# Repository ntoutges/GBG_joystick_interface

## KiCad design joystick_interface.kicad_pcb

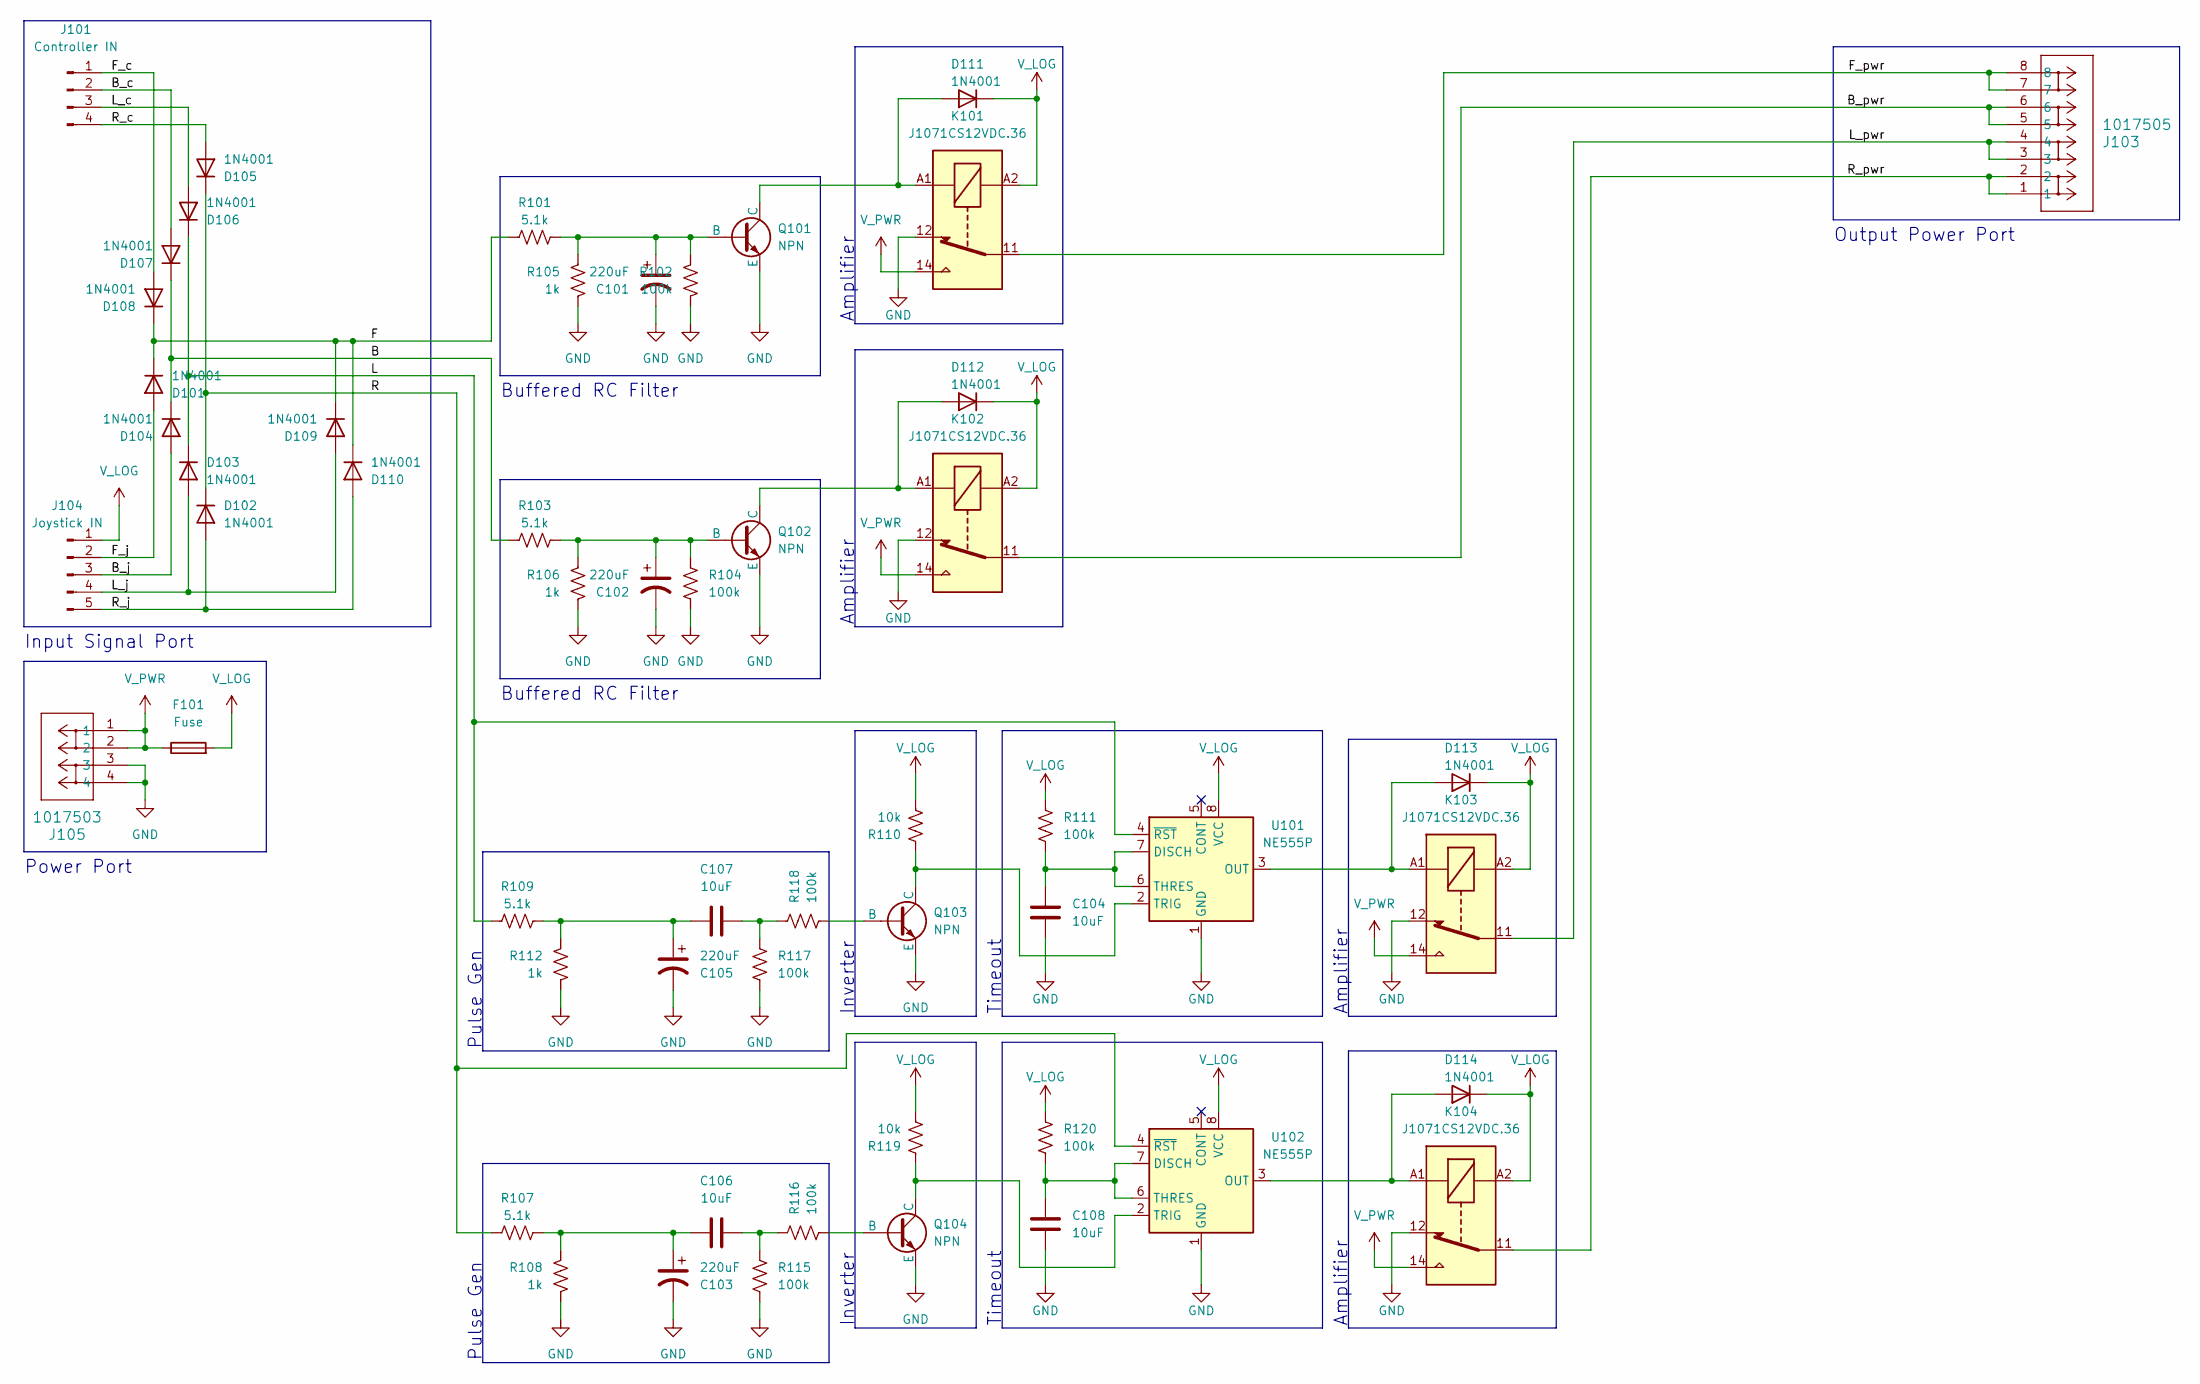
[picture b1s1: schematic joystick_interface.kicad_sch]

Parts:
C101, C102, C103, C105: 220uF; C_Radial_D5.0mm_H11.0mm_P2.00mm
C104, C106, C107, C108: 10uF; C_Disc_D3.4mm_W2.1mm_P2.50mm
D101, D102, D103, D104, D105, D106, D107, D108, D109, D110, D111, D112, D113, D114: 1N4001; D_DO-41_SOD81_P10.16mm_Horizontal
F101: Fuse; Fuseholder_Clip-5x20mm_Eaton_1A5601-01_Inline_P20.80x6.76mm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
J101: Controller IN; JST_EH_B4B-EH-A_1x04_P2.50mm_Vertical
J103: 1017505; CONN_1017493
J104: Joystick IN; JST_EH_B5B-EH-A_1x05_P2.50mm_Vertical
J105: 1017503; CONN_1017491
K101, K102, K103, K104: J1071CS12VDC.36; Relay_SPDT_Hongfa_HF3F-L-xx-1ZL1T
Q101, Q102, Q103, Q104: NPN; TO-92_Wide
R101, R103: 5.1k; R_Axial_DIN0207_L6.3mm_D2.5mm_P10.16mm_Horizontal
R102, R104: 100k; R_Axial_DIN0207_L6.3mm_D2.5mm_P10.16mm_Horizontal
R105, R106: 1k; R_Axial_DIN0207_L6.3mm_D2.5mm_P10.16mm_Horizontal
R107, R109: 5.1k; R_Axial_DIN0204_L3.6mm_D1.6mm_P1.90mm_Vertical
R108, R112: 1k; R_Axial_DIN0204_L3.6mm_D1.6mm_P1.90mm_Vertical
R110, R119: 10k; R_Axial_DIN0204_L3.6mm_D1.6mm_P1.90mm_Vertical
R111, R115, R116, R117, R118, R120: 100k; R_Axial_DIN0204_L3.6mm_D1.6mm_P1.90mm_Vertical
U101, U102: NE555P; DIP-8_W7.62mm

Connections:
/B: D104.1 (K), D107.1 (K), R103.1
/B_c: D107.2 (A), J101.2
/B_j: D104.2 (A), J104.3
/B_pwr: J103.5, J103.6, K102.11
/F: D101.1 (K), D108.1 (K), D109.1 (K), D110.1 (K), R101.1
/F_c: D108.2 (A), J101.1
/F_j: D101.2 (A), J104.2
/F_pwr: J103.7, J103.8, K101.11
/L: D103.1 (K), D106.1 (K), R109.1, U101.4 (~RST)
/L_c: D106.2 (A), J101.3
/L_j: D103.2 (A), D109.2 (A), J104.4
/L_pwr: J103.3, J103.4, K103.11
/R: D102.1 (K), D105.1 (K), R107.1, U102.4 (~RST)
/R_c: D105.2 (A), J101.4
/R_j: D102.2 (A), D110.2 (A), J104.5
/R_pwr: J103.1, J103.2, K104.11
GND: C101.2, C102.2, C103.2, C104.1, C105.2, C108.1, J105.3, J105.4, K101.12, K102.12, K103.12, K104.12, Q101.3 (E), Q102.3 (E), Q103.3 (E), Q104.3 (E), R102.1, R104.1, R105.2, R106.2, R108.2, R112.2, R115.1, R117.1, U101.1 (GND), U102.1 (GND)
unnamed: C103.1, C106.1, R107.2, R108.1
unnamed: C105.1, C107.1, R109.2, R112.1
unnamed: C106.2, R115.2, R116.2
unnamed: C107.2, R117.2, R118.2
unnamed: D111.2 (A), K101.A1, Q101.1 (C)
unnamed: D112.2 (A), K102.A1, Q102.1 (C)
unnamed: D113.2 (A), K103.A1, U101.3 (OUT)
unnamed: D114.2 (A), K104.A1, U102.3 (OUT)
unnamed: C101.1, Q101.2 (B), R101.2, R102.2, R105.1
unnamed: C102.1, Q102.2 (B), R103.2, R104.2, R106.1
unnamed: Q103.2 (B), R118.1
unnamed: Q103.1 (C), R110.1, U101.2 (TRIG)
unnamed: Q104.2 (B), R116.1
unnamed: Q104.1 (C), R119.1, U102.2 (TRIG)
unnamed: C104.2, R111.2, U101.6 (THRES), U101.7 (DISCH)
unnamed: C108.2, R120.2, U102.6 (THRES), U102.7 (DISCH)
V_LOG: D111.1 (K), D112.1 (K), D113.1 (K), D114.1 (K), F101.2, J104.1, K101.A2, K102.A2, K103.A2, K104.A2, R110.2, R111.1, R119.2, R120.1, U101.8 (VCC), U102.8 (VCC)
V_PWR: F101.1, J105.1, J105.2, K101.14, K102.14, K103.14, K104.14

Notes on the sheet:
Amplifier
Buffered RC Filter
Power Port
Inverter
Input Signal Port
Pulse Gen
Output Power Port
Timeout

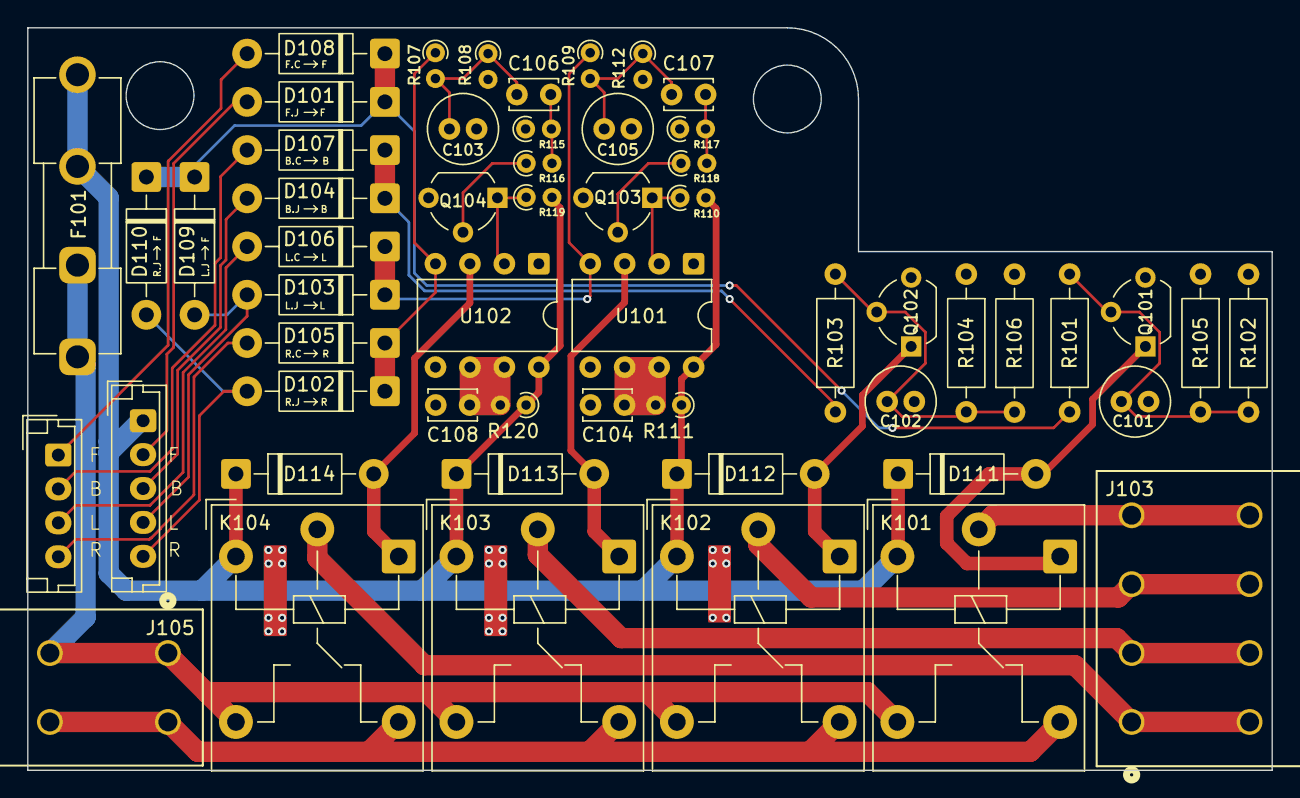
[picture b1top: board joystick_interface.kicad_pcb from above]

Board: 2 copper layers, 91.8 x 54.8 mm, 55 parts (0 on the bottom side), 35 nets.
